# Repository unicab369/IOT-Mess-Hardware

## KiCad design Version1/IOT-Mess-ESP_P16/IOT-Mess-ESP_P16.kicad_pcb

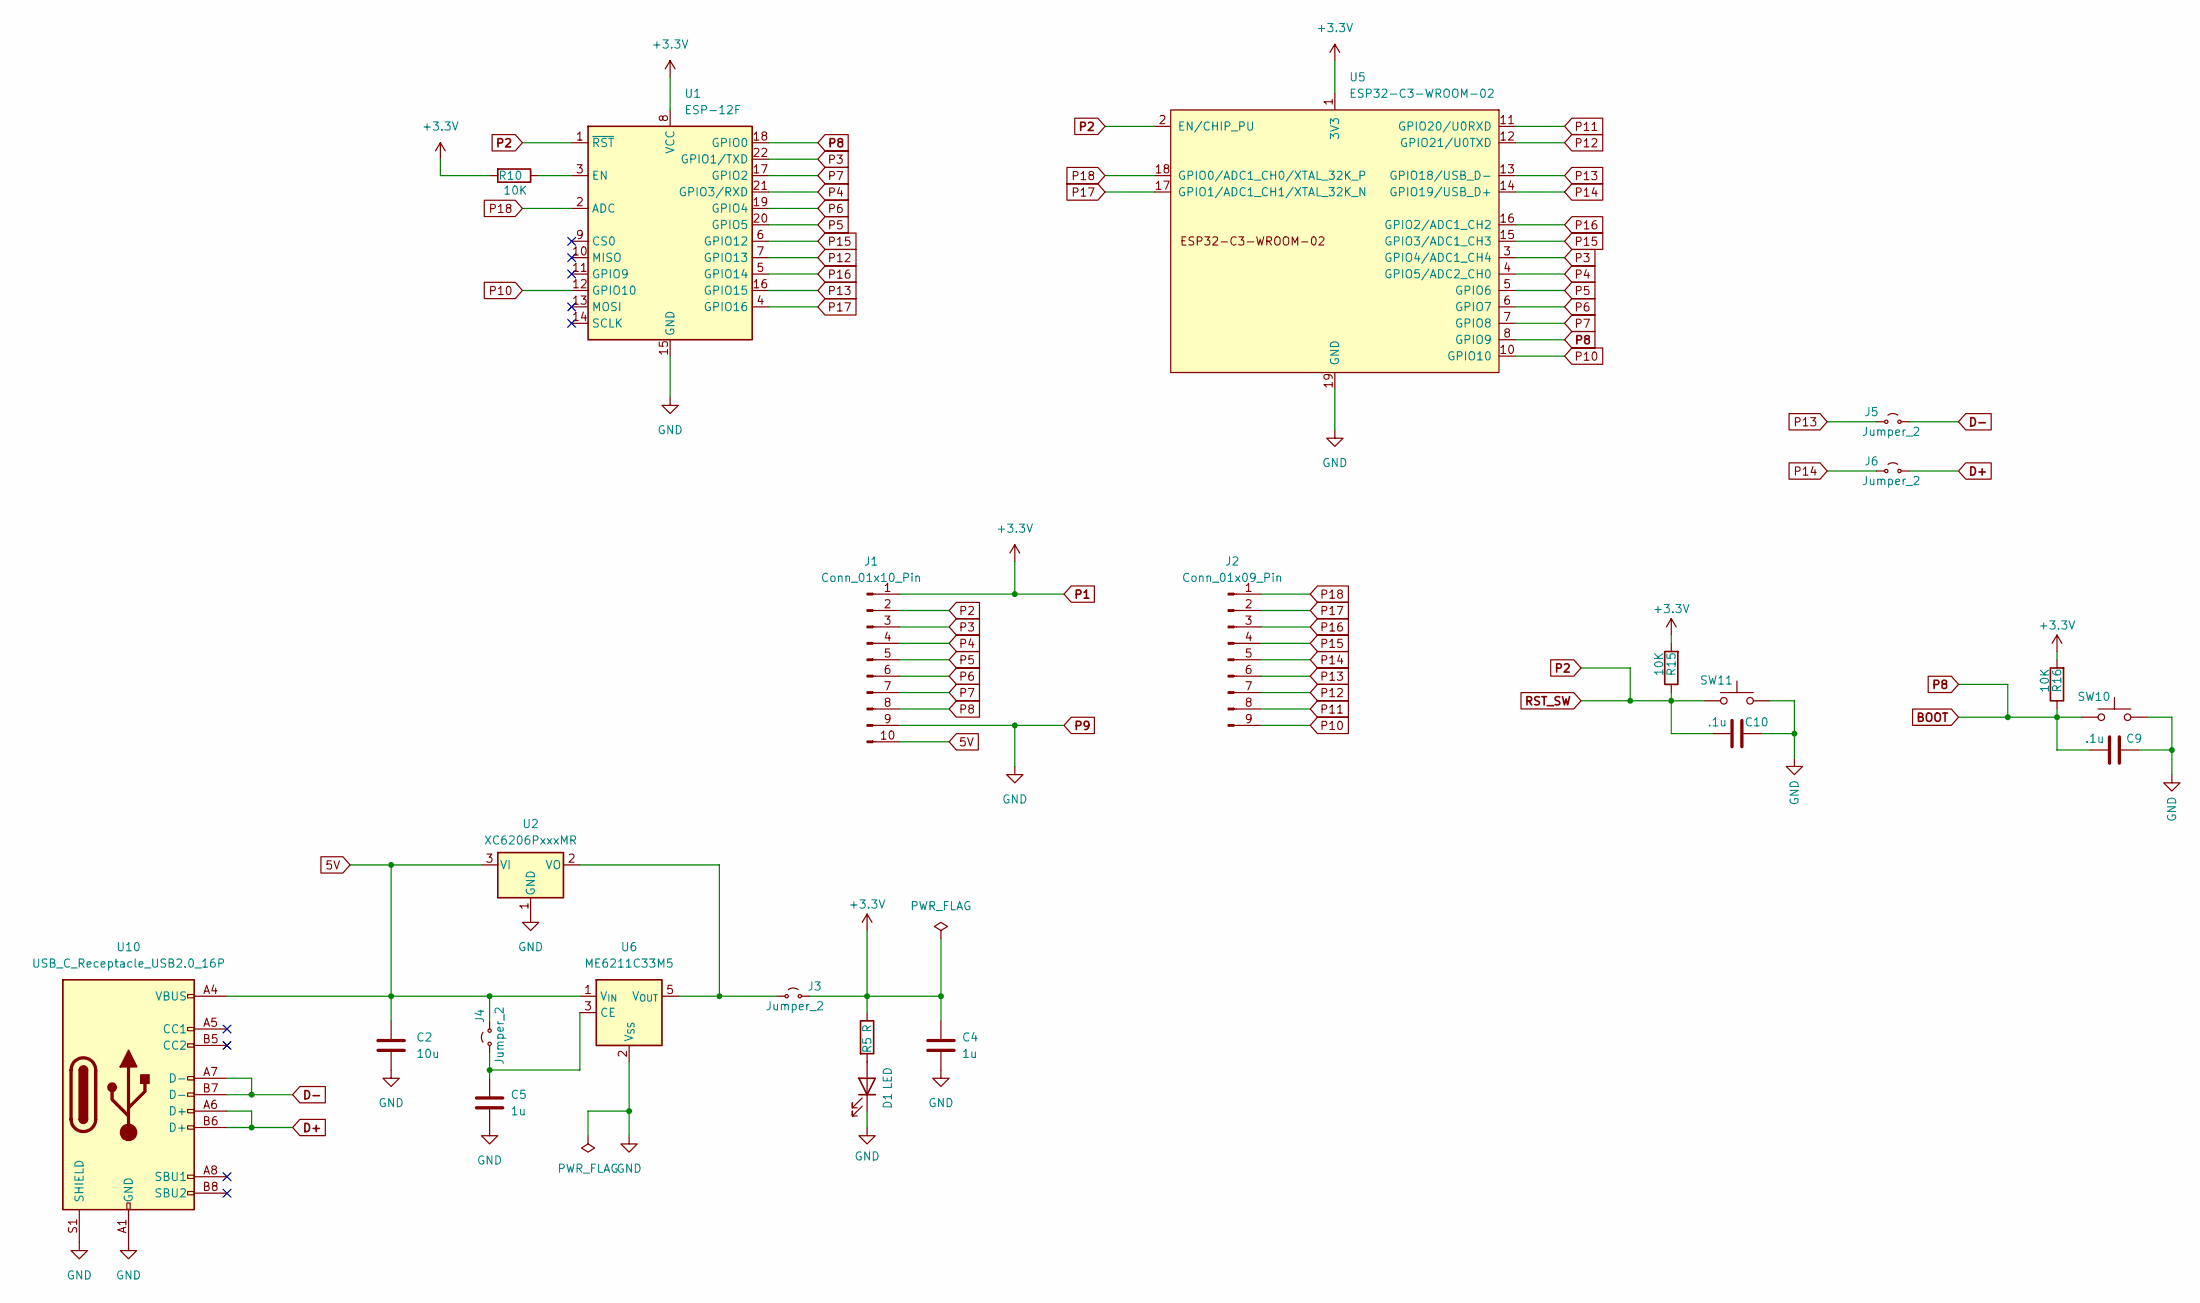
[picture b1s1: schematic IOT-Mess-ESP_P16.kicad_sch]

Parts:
C2: 10u; C_0603_1608Metric
C4, C5: 1u; C_0603_1608Metric
C9, C10: .1u; C_0603_1608Metric
D1: LED; LED_0603_1608Metric
J1: Conn_01x10_Pin; PinHeader_1x10_P2.54mm_Vertical
J2: Conn_01x09_Pin; PinHeader_1x09_P2.54mm_Vertical
J3, J4, J5, J6: Jumper_2; Jumpper-triangle
R5: R; R_0603_1608Metric
R10, R15, R16: 10K; R_0603_1608Metric
SW10, SW11: SW_Push; SW_SPST_PTS810
U1: ESP-12F; ESP-12E
U2: XC6206PxxxMR; SOT-23-3
U5: ESP32-C3-WROOM-02
U6: ME6211C33M5; SOT-23-5
U10: USB_C_Receptacle_USB2.0_16P; USB_C_Receptacle_HRO_TYPE-C-31-M-12

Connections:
5V: C2.1, J1.10, J4.1 (A), U2.3 (VI), U6.1 (V_{IN}), U10.A4 (VBUS), U10.A9 (VBUS), U10.B4 (VBUS), U10.B9 (VBUS)
BOOT: C9.1, J1.8, R16.1, SW10.1, U1.18 (GPIO0), U5.8 (GPIO9)
D+: J6.2 (B), U10.A6 (D+), U10.B6 (D+)
D-: J5.2 (B), U10.A7 (D-), U10.B7 (D-)
unnamed: D1.2 (A), R5.2
unnamed: J3.2 (B), U2.2 (VO), U6.5 (V_{OUT})
unnamed: C5.1, J4.2 (B), U6.3 (CE)
unnamed: R10.1, U1.3 (EN)
P1: C4.1, J1.1, J3.1 (A), R5.1, R10.2, R15.2, R16.2, U1.8 (VCC), U5.1 (3V3)
P2: C10.1, J1.2, R15.1, SW11.1, U1.1 (~RST), U5.2 (EN/CHIP_PU)
P3: J1.3, U1.22 (GPIO1/TXD), U5.3 (GPIO4/ADC1_CH4)
P4: J1.4, U1.21 (GPIO3/RXD), U5.4 (GPIO5/ADC2_CH0)
P5: J1.5, U1.20 (GPIO5), U5.5 (GPIO6)
P6: J1.6, U1.19 (GPIO4), U5.6 (GPIO7)
P7: J1.7, U1.17 (GPIO2), U5.7 (GPIO8)
P9: C2.2, C4.2, C5.2, C9.2, C10.2, D1.1 (K), J1.9, SW10.2, SW11.2, U1.15 (GND), U2.1 (GND), U5.9 (GND), U5.19 (GND), U6.2 (V_{SS}), U10.A1 (GND), U10.A12 (GND), U10.B1 (GND), U10.B12 (GND), U10.S1 (SHIELD)
P10: J2.9, U1.12 (GPIO10), U5.10 (GPIO10)
P11: J2.8, U5.11 (GPIO20/U0RXD)
P12: J2.7, U1.7 (GPIO13), U5.12 (GPIO21/U0TXD)
P13: J2.6, J5.1 (A), U1.16 (GPIO15), U5.13 (GPIO18/USB_D-)
P14: J2.5, J6.1 (A), U5.14 (GPIO19/USB_D+)
P15: J2.4, U1.6 (GPIO12), U5.15 (GPIO3/ADC1_CH3)
P16: J2.3, U1.5 (GPIO14), U5.16 (GPIO2/ADC1_CH2)
P17: J2.2, U1.4 (GPIO16), U5.17 (GPIO1/ADC1_CH1/XTAL_32K_N)
P18: J2.1, U1.2 (ADC), U5.18 (GPIO0/ADC1_CH0/XTAL_32K_P)

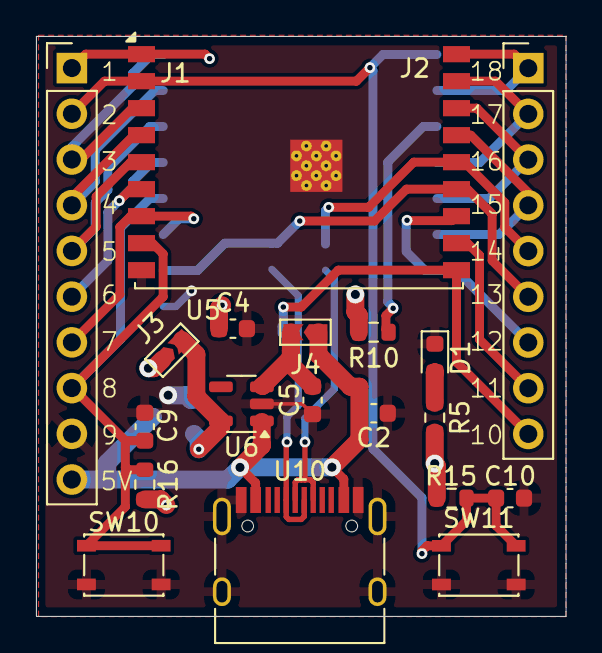
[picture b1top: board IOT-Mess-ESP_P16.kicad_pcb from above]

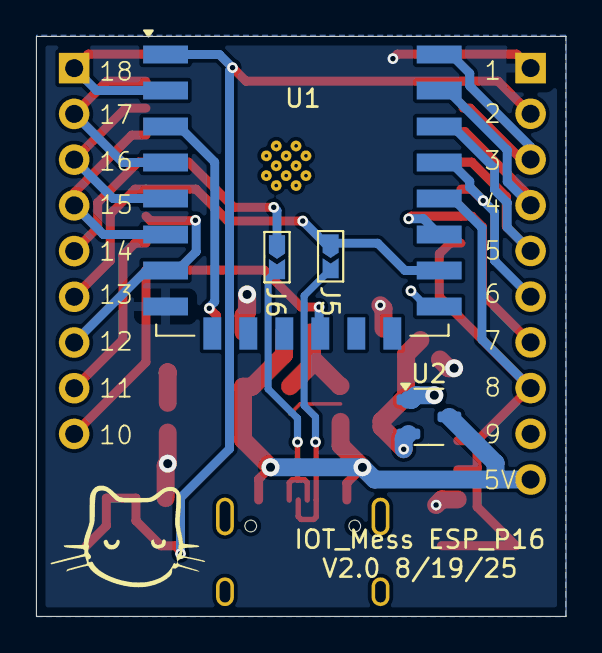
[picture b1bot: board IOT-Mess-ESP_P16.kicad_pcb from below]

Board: 2 copper layers, 29.4 x 32.2 mm, 23 parts (4 on the bottom side), 25 nets.

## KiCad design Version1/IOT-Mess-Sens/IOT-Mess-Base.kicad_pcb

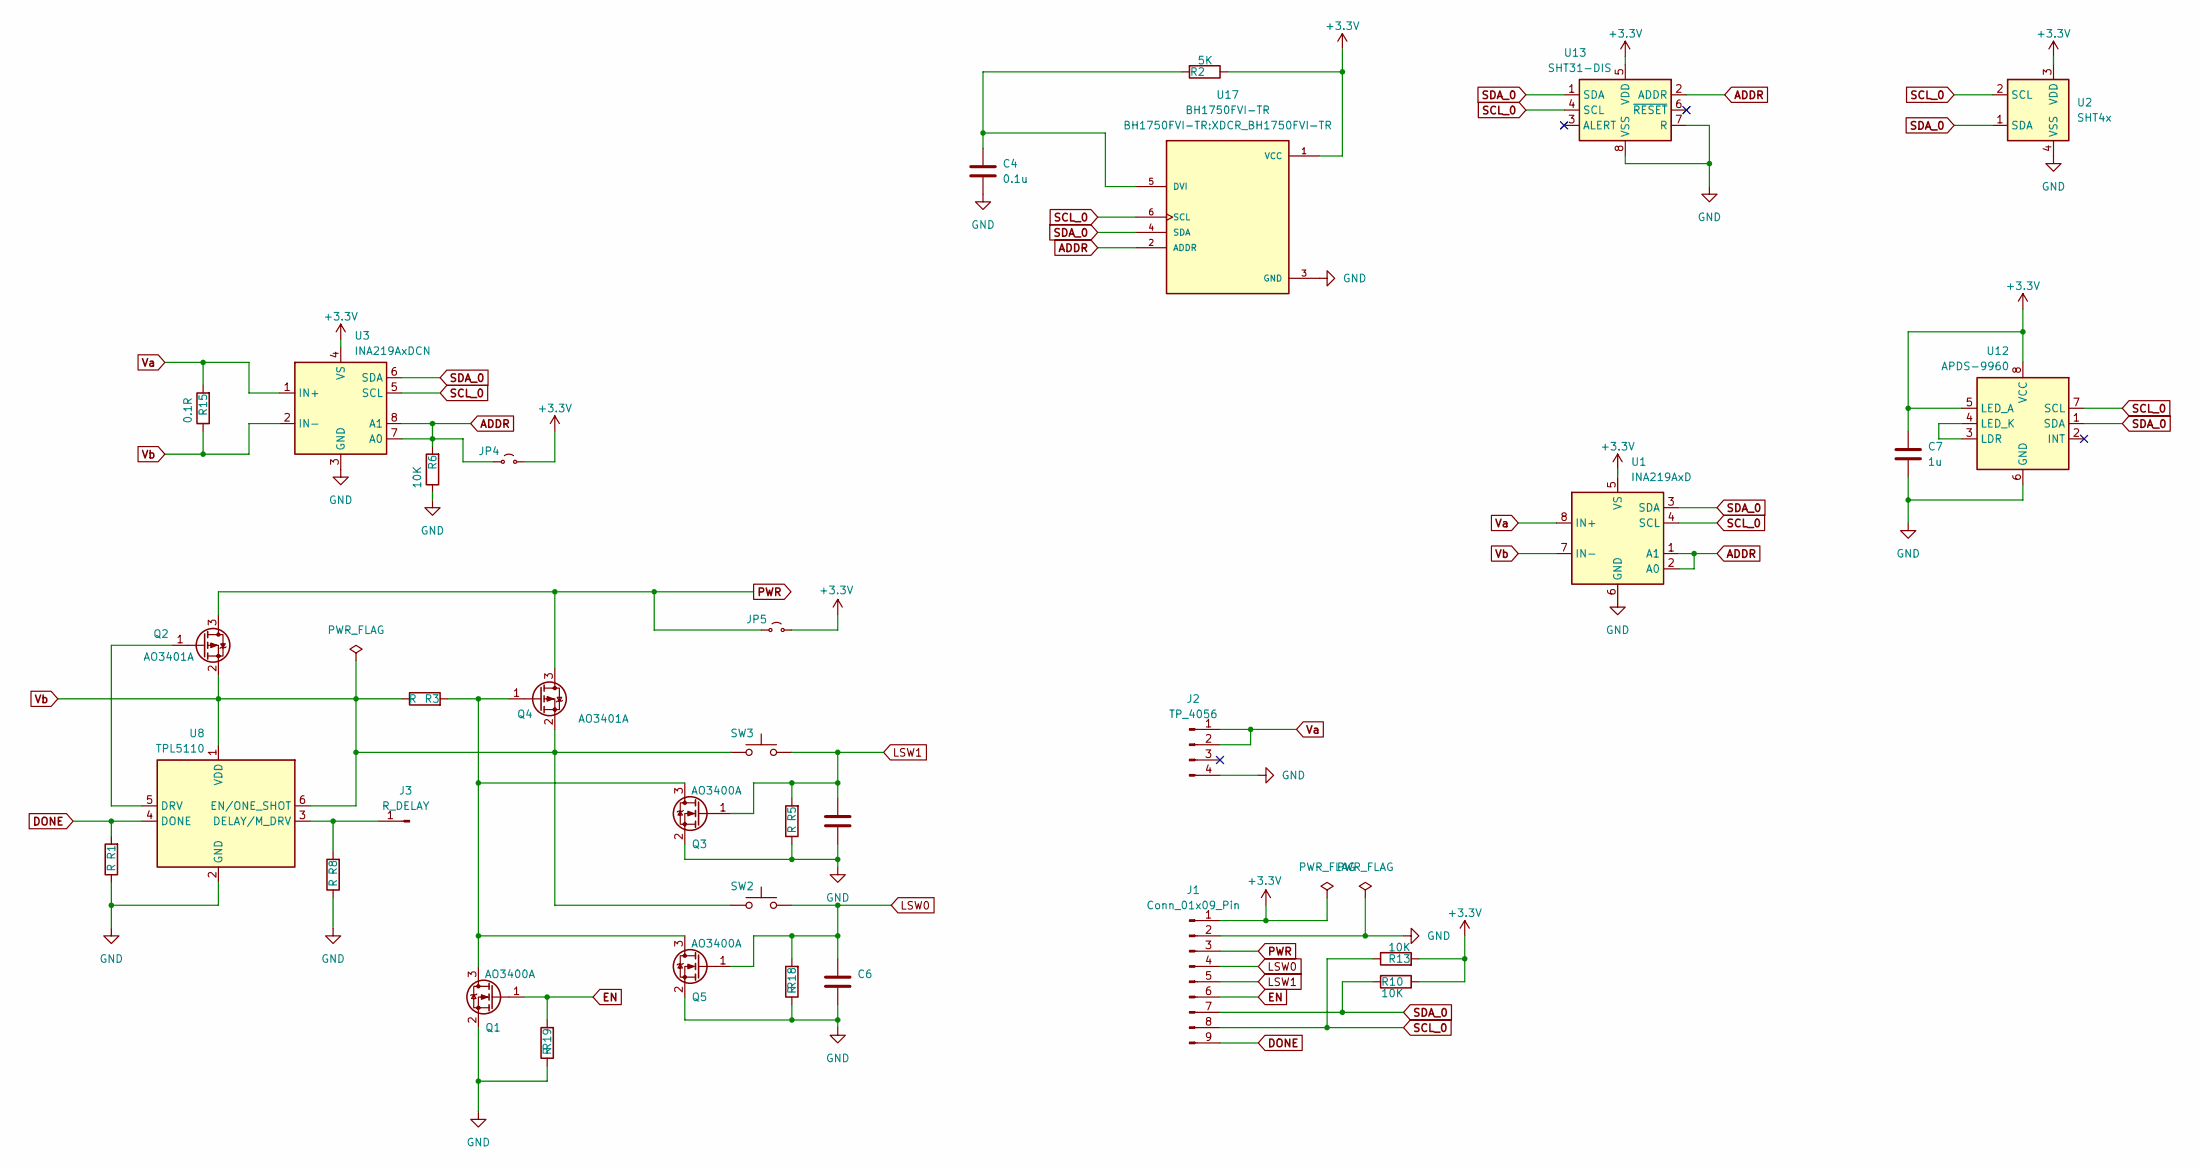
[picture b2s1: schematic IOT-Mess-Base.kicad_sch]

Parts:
C4: 0.1u; C_0603_1608Metric
C5, C6: C; C_0603_1608Metric
C7: 1u; C_0603_1608Metric
J1: Conn_01x09_Pin; PinHeader_1x09_P2.54mm_Vertical
J2: TP_4056; TP_Charger
J3: R_DELAY; PinHeader_1x01_P1.00mm_Vertical
JP4, JP5: Jp_2; SolderJumper-2_P1.3mm_Open_Pad1.0x1.5mm
Q1, Q3, Q5: AO3400A; SOT-23
Q2, Q4: AO3401A; SOT-23
R1, R3, R5, R8, R18, R19: R; R_0603_1608Metric
R2: 5K; R_0603_1608Metric
R6, R10, R13: 10K; R_0603_1608Metric
R15: 0.1R; R_2512_6332Metric
SW2, SW3: SW_Push; SW_SPST_PTS810
U1: INA219AxD; SOIC-8_3.9x4.9mm_P1.27mm
U2: SHT4x; Sensirion_DFN-4_1.5x1.5mm_P0.8mm_SHT4x_NoCentralPad
U3: INA219AxDCN; SOT-23-8
U8: TPL5110; SOT-23-6
U12: APDS-9960; Avago_APDS-9960
U13: SHT31-DIS; Sensirion_DFN-8-1EP_2.5x2.5mm_P0.5mm_EP1.1x1.7mm
U17: BH1750FVI-TR; XDCR_BH1750FVI-TR; PARTREV D

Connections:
+3.3V: C7.1, J1.1, JP4.2 (B), JP5.2 (B), R2.1, R10.1, R13.2, U1.5 (VS), U2.3 (VDD), U3.4 (VS), U12.5 (LED_A), U12.8 (VCC), U13.5 (VDD), U17.1 (VCC)
ADDR: JP4.1 (A), R6.2, U1.1 (A1), U1.2 (A0), U3.7 (A0), U3.8 (A1), U13.2 (ADDR), U17.2 (ADDR)
DONE: J1.9, R1.2, U8.4 (DONE)
EN: J1.6, Q1.1 (G), R19.2
GND: C4.2, C5.2, C6.2, C7.2, J1.2, J2.4, Q1.2 (S), Q3.2 (S), Q5.2 (S), R1.1, R5.1, R6.1, R8.1, R18.1, R19.1, U1.6 (GND), U2.4 (VSS), U3.3 (GND), U8.2 (GND), U12.6 (GND), U13.7 (R), U13.8 (VSS), U13.9 (VSS), U17.3 (GND)
LSW0: C6.1, J1.4, Q5.1 (G), R18.2, SW2.2
LSW1: C5.1, J1.5, Q3.1 (G), R5.2, SW3.2
unnamed: J3.1, R8.2, U8.3 (DELAY/M_DRV)
unnamed: Q1.3 (D), Q3.3 (D), Q4.1 (G), Q5.3 (D), R3.2
unnamed: Q2.1 (G), U8.5 (DRV)
unnamed: U12.3 (LDR), U12.4 (LED_K)
unnamed: C4.1, R2.2, U17.5 (DVI)
PWR: J1.3, JP5.1 (A), Q2.3 (D), Q4.3 (D)
SCL_0: J1.8, R13.1, U1.4 (SCL), U2.2 (SCL), U3.5 (SCL), U12.7 (SCL), U13.4 (SCL), U17.6 (SCL)
SDA_0: J1.7, R10.2, U1.3 (SDA), U2.1 (SDA), U3.6 (SDA), U12.1 (SDA), U13.1 (SDA), U17.4 (SDA)
Va: J2.1, J2.2, R15.2, U1.8 (IN+), U3.1 (IN+)
Vb: Q2.2 (S), Q4.2 (S), R3.1, R15.1, SW2.1, SW3.1, U1.7 (IN-), U3.2 (IN-), U8.1 (VDD), U8.6 (EN/ONE_SHOT)

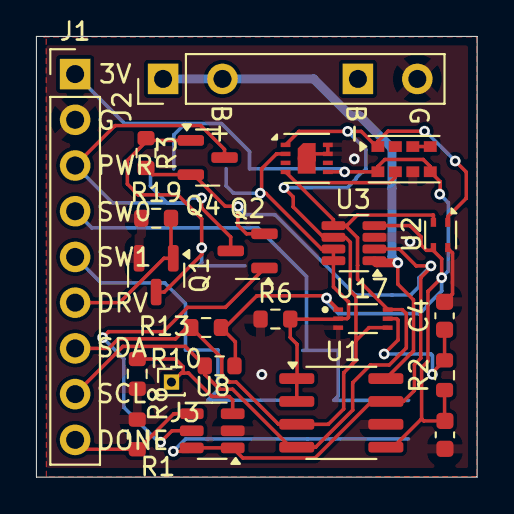
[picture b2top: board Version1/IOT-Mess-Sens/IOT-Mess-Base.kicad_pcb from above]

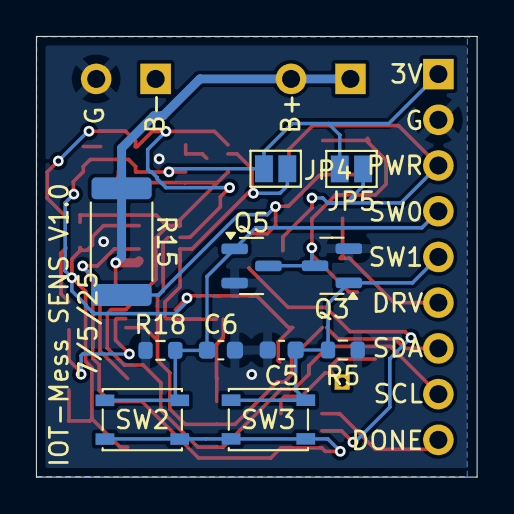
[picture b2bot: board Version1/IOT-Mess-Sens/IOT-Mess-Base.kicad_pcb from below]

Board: 2 copper layers, 24.5 x 24.5 mm, 34 parts (11 on the bottom side), 17 nets.

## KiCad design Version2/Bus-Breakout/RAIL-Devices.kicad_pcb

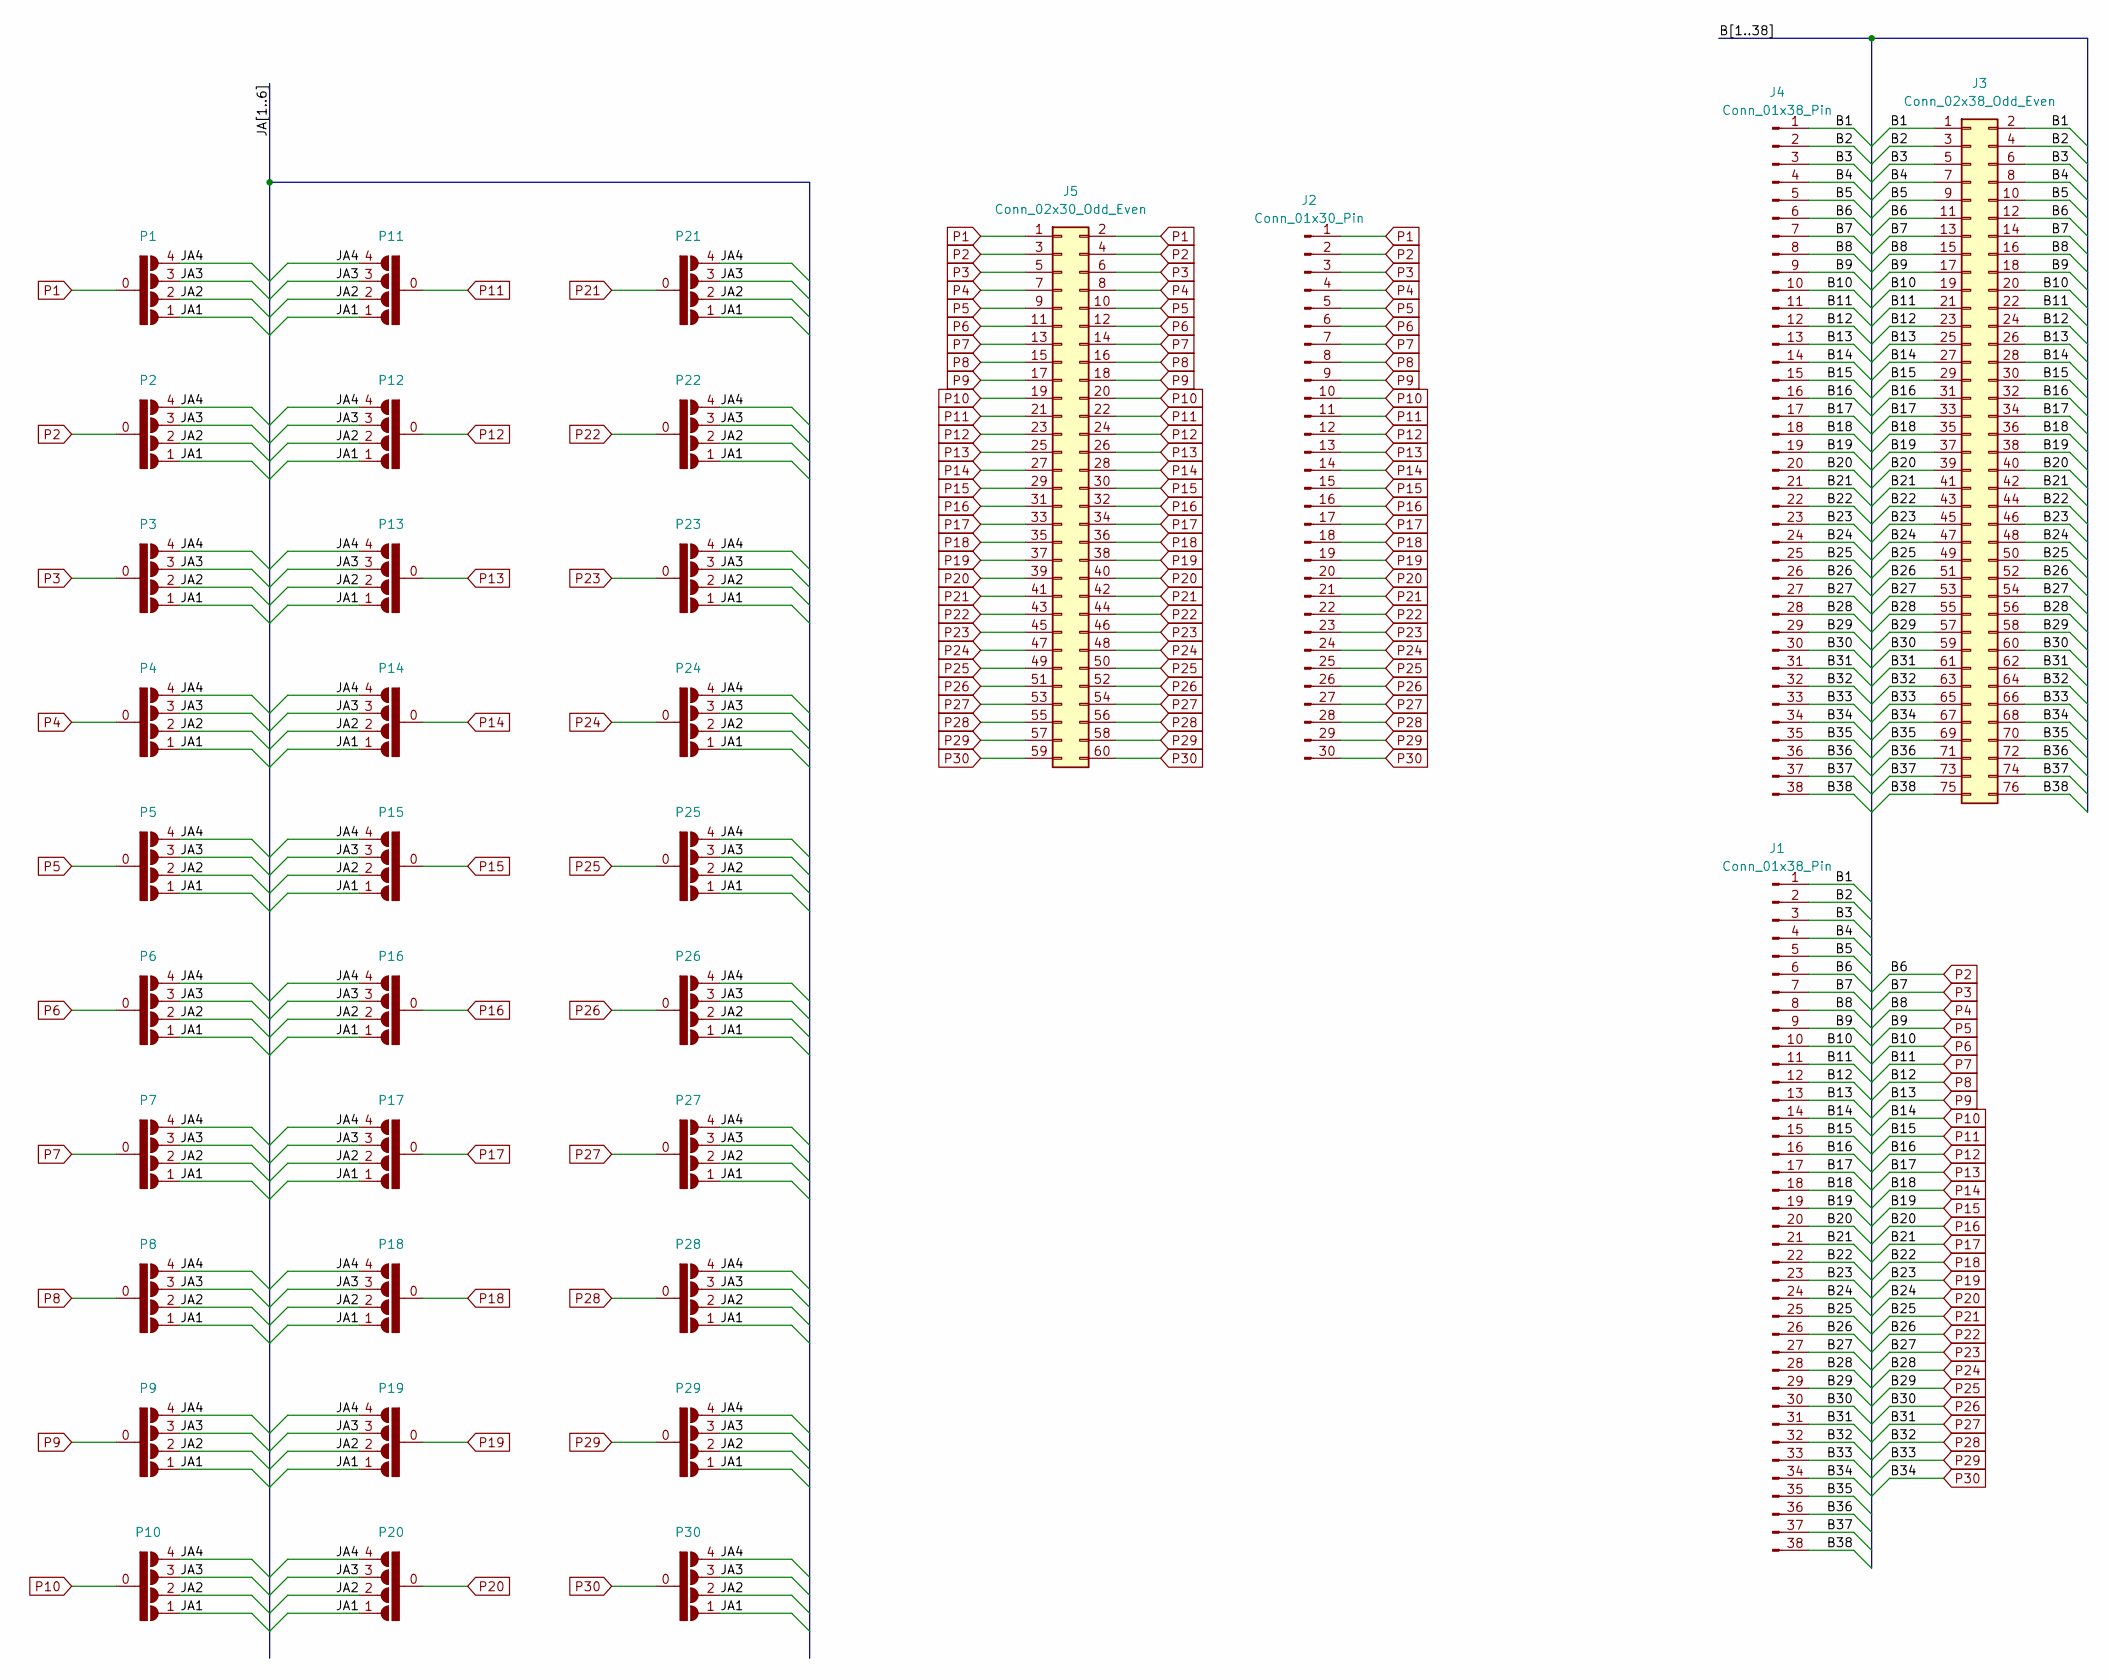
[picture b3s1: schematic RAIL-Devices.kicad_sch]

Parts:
J1, J4: Conn_01x38_Pin; PinSocket_1x38_P2.54mm_Vertical
J2: Conn_01x30_Pin; PinSocket_1x30_P2.54mm_Vertical
J3: Conn_02x38_Odd_Even; PinSocket_2x38_P2.54mm_Vertical
J5: Conn_02x30_Odd_Even; PinSocket_2x30_P2.54mm_Vertical
P1, P2, P3, P4, P5, P6, P7, P8, P9, P10, P11, P12, P13, P14, P15, P16, P17, P18, P19, P20, P21, P22, P23, P24, P25, P26, P27, P28, P29, P30: Jumper4x1

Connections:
/B1: J1.1, J3.1, J3.2, J4.1
/B2: J1.2, J3.3, J3.4, J4.2
/B3: J1.3, J3.5, J3.6, J4.3
/B4: J1.4, J3.7, J3.8, J4.4
/B5: J1.5, J3.9, J3.10, J4.5
/B35: J1.35, J3.69, J3.70, J4.35
/B36: J1.36, J3.71, J3.72, J4.36
/B37: J1.37, J3.73, J3.74, J4.37
/B38: J1.38, J3.75, J3.76, J4.38
/JA1: P1.1 (B), P2.1 (B), P3.1 (B), P4.1 (B), P5.1 (B), P6.1 (B), P7.1 (B), P8.1 (B), P9.1 (B), P10.1 (B), P11.1 (B), P12.1 (B), P13.1 (B), P14.1 (B), P15.1 (B), P16.1 (B), P17.1 (B), P18.1 (B), P19.1 (B), P20.1 (B), P21.1 (B), P22.1 (B), P23.1 (B), P24.1 (B), P25.1 (B), P26.1 (B), P27.1 (B), P28.1 (B), P29.1 (B), P30.1 (B)
/JA2: P1.2 (B), P2.2 (B), P3.2 (B), P4.2 (B), P5.2 (B), P6.2 (B), P7.2 (B), P8.2 (B), P9.2 (B), P10.2 (B), P11.2 (B), P12.2 (B), P13.2 (B), P14.2 (B), P15.2 (B), P16.2 (B), P17.2 (B), P18.2 (B), P19.2 (B), P20.2 (B), P21.2 (B), P22.2 (B), P23.2 (B), P24.2 (B), P25.2 (B), P26.2 (B), P27.2 (B), P28.2 (B), P29.2 (B), P30.2 (B)
/JA3: P1.3 (B), P2.3 (B), P3.3 (B), P4.3 (B), P5.3 (B), P6.3 (B), P7.3 (B), P8.3 (B), P9.3 (B), P10.3 (B), P11.3 (B), P12.3 (B), P13.3 (B), P14.3 (B), P15.3 (B), P16.3 (B), P17.3 (B), P18.3 (B), P19.3 (B), P20.3 (B), P21.3 (B), P22.3 (B), P23.3 (B), P24.3 (B), P25.3 (B), P26.3 (B), P27.3 (B), P28.3 (B), P29.3 (B), P30.3 (B)
/JA4: P1.4 (B), P2.4 (B), P3.4 (B), P4.4 (B), P5.4 (B), P6.4 (B), P7.4 (B), P8.4 (B), P9.4 (B), P10.4 (B), P11.4 (B), P12.4 (B), P13.4 (B), P14.4 (B), P15.4 (B), P16.4 (B), P17.4 (B), P18.4 (B), P19.4 (B), P20.4 (B), P21.4 (B), P22.4 (B), P23.4 (B), P24.4 (B), P25.4 (B), P26.4 (B), P27.4 (B), P28.4 (B), P29.4 (B), P30.4 (B)
P1: J2.1, J5.1, J5.2, P1.0 (C)
P2: J1.6, J2.2, J3.11, J3.12, J4.6, J5.3, J5.4, P2.0 (C)
P3: J1.7, J2.3, J3.13, J3.14, J4.7, J5.5, J5.6, P3.0 (C)
P4: J1.8, J2.4, J3.15, J3.16, J4.8, J5.7, J5.8, P4.0 (C)
P5: J1.9, J2.5, J3.17, J3.18, J4.9, J5.9, J5.10, P5.0 (C)
P6: J1.10, J2.6, J3.19, J3.20, J4.10, J5.11, J5.12, P6.0 (C)
P7: J1.11, J2.7, J3.21, J3.22, J4.11, J5.13, J5.14, P7.0 (C)
P8: J1.12, J2.8, J3.23, J3.24, J4.12, J5.15, J5.16, P8.0 (C)
P9: J1.13, J2.9, J3.25, J3.26, J4.13, J5.17, J5.18, P9.0 (C)
P10: J1.14, J2.10, J3.27, J3.28, J4.14, J5.19, J5.20, P10.0 (C)
P11: J1.15, J2.11, J3.29, J3.30, J4.15, J5.21, J5.22, P11.0 (C)
P12: J1.16, J2.12, J3.31, J3.32, J4.16, J5.23, J5.24, P12.0 (C)
P13: J1.17, J2.13, J3.33, J3.34, J4.17, J5.25, J5.26, P13.0 (C)
P14: J1.18, J2.14, J3.35, J3.36, J4.18, J5.27, J5.28, P14.0 (C)
P15: J1.19, J2.15, J3.37, J3.38, J4.19, J5.29, J5.30, P15.0 (C)
P16: J1.20, J2.16, J3.39, J3.40, J4.20, J5.31, J5.32, P16.0 (C)
P17: J1.21, J2.17, J3.41, J3.42, J4.21, J5.33, J5.34, P17.0 (C)
P18: J1.22, J2.18, J3.43, J3.44, J4.22, J5.35, J5.36, P18.0 (C)
P19: J1.23, J2.19, J3.45, J3.46, J4.23, J5.37, J5.38, P19.0 (C)
P20: J1.24, J2.20, J3.47, J3.48, J4.24, J5.39, J5.40, P20.0 (C)
P21: J1.25, J2.21, J3.49, J3.50, J4.25, J5.41, J5.42, P21.0 (C)
P22: J1.26, J2.22, J3.51, J3.52, J4.26, J5.43, J5.44, P22.0 (C)
P23: J1.27, J2.23, J3.53, J3.54, J4.27, J5.45, J5.46, P23.0 (C)
P24: J1.28, J2.24, J3.55, J3.56, J4.28, J5.47, J5.48, P24.0 (C)
P25: J1.29, J2.25, J3.57, J3.58, J4.29, J5.49, J5.50, P25.0 (C)
P26: J1.30, J2.26, J3.59, J3.60, J4.30, J5.51, J5.52, P26.0 (C)
P27: J1.31, J2.27, J3.61, J3.62, J4.31, J5.53, J5.54, P27.0 (C)
P28: J1.32, J2.28, J3.63, J3.64, J4.32, J5.55, J5.56, P28.0 (C)
P29: J1.33, J2.29, J3.65, J3.66, J4.33, J5.57, J5.58, P29.0 (C)
P30: J1.34, J2.30, J3.67, J3.68, J4.34, J5.59, J5.60, P30.0 (C)

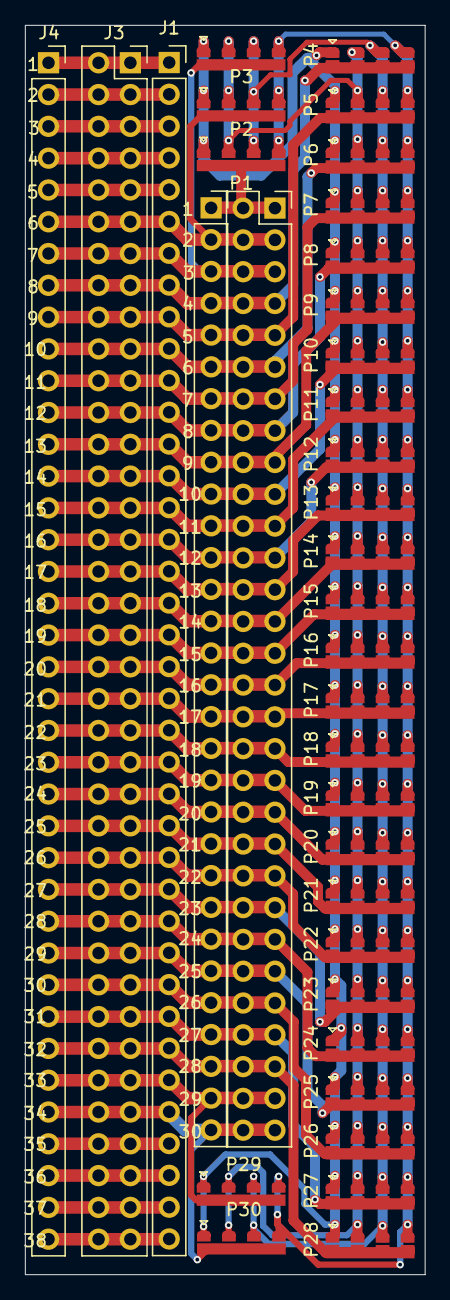
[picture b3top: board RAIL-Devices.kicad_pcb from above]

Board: 2 copper layers, 31.9 x 99.8 mm, 35 parts (0 on the bottom side), 43 nets.

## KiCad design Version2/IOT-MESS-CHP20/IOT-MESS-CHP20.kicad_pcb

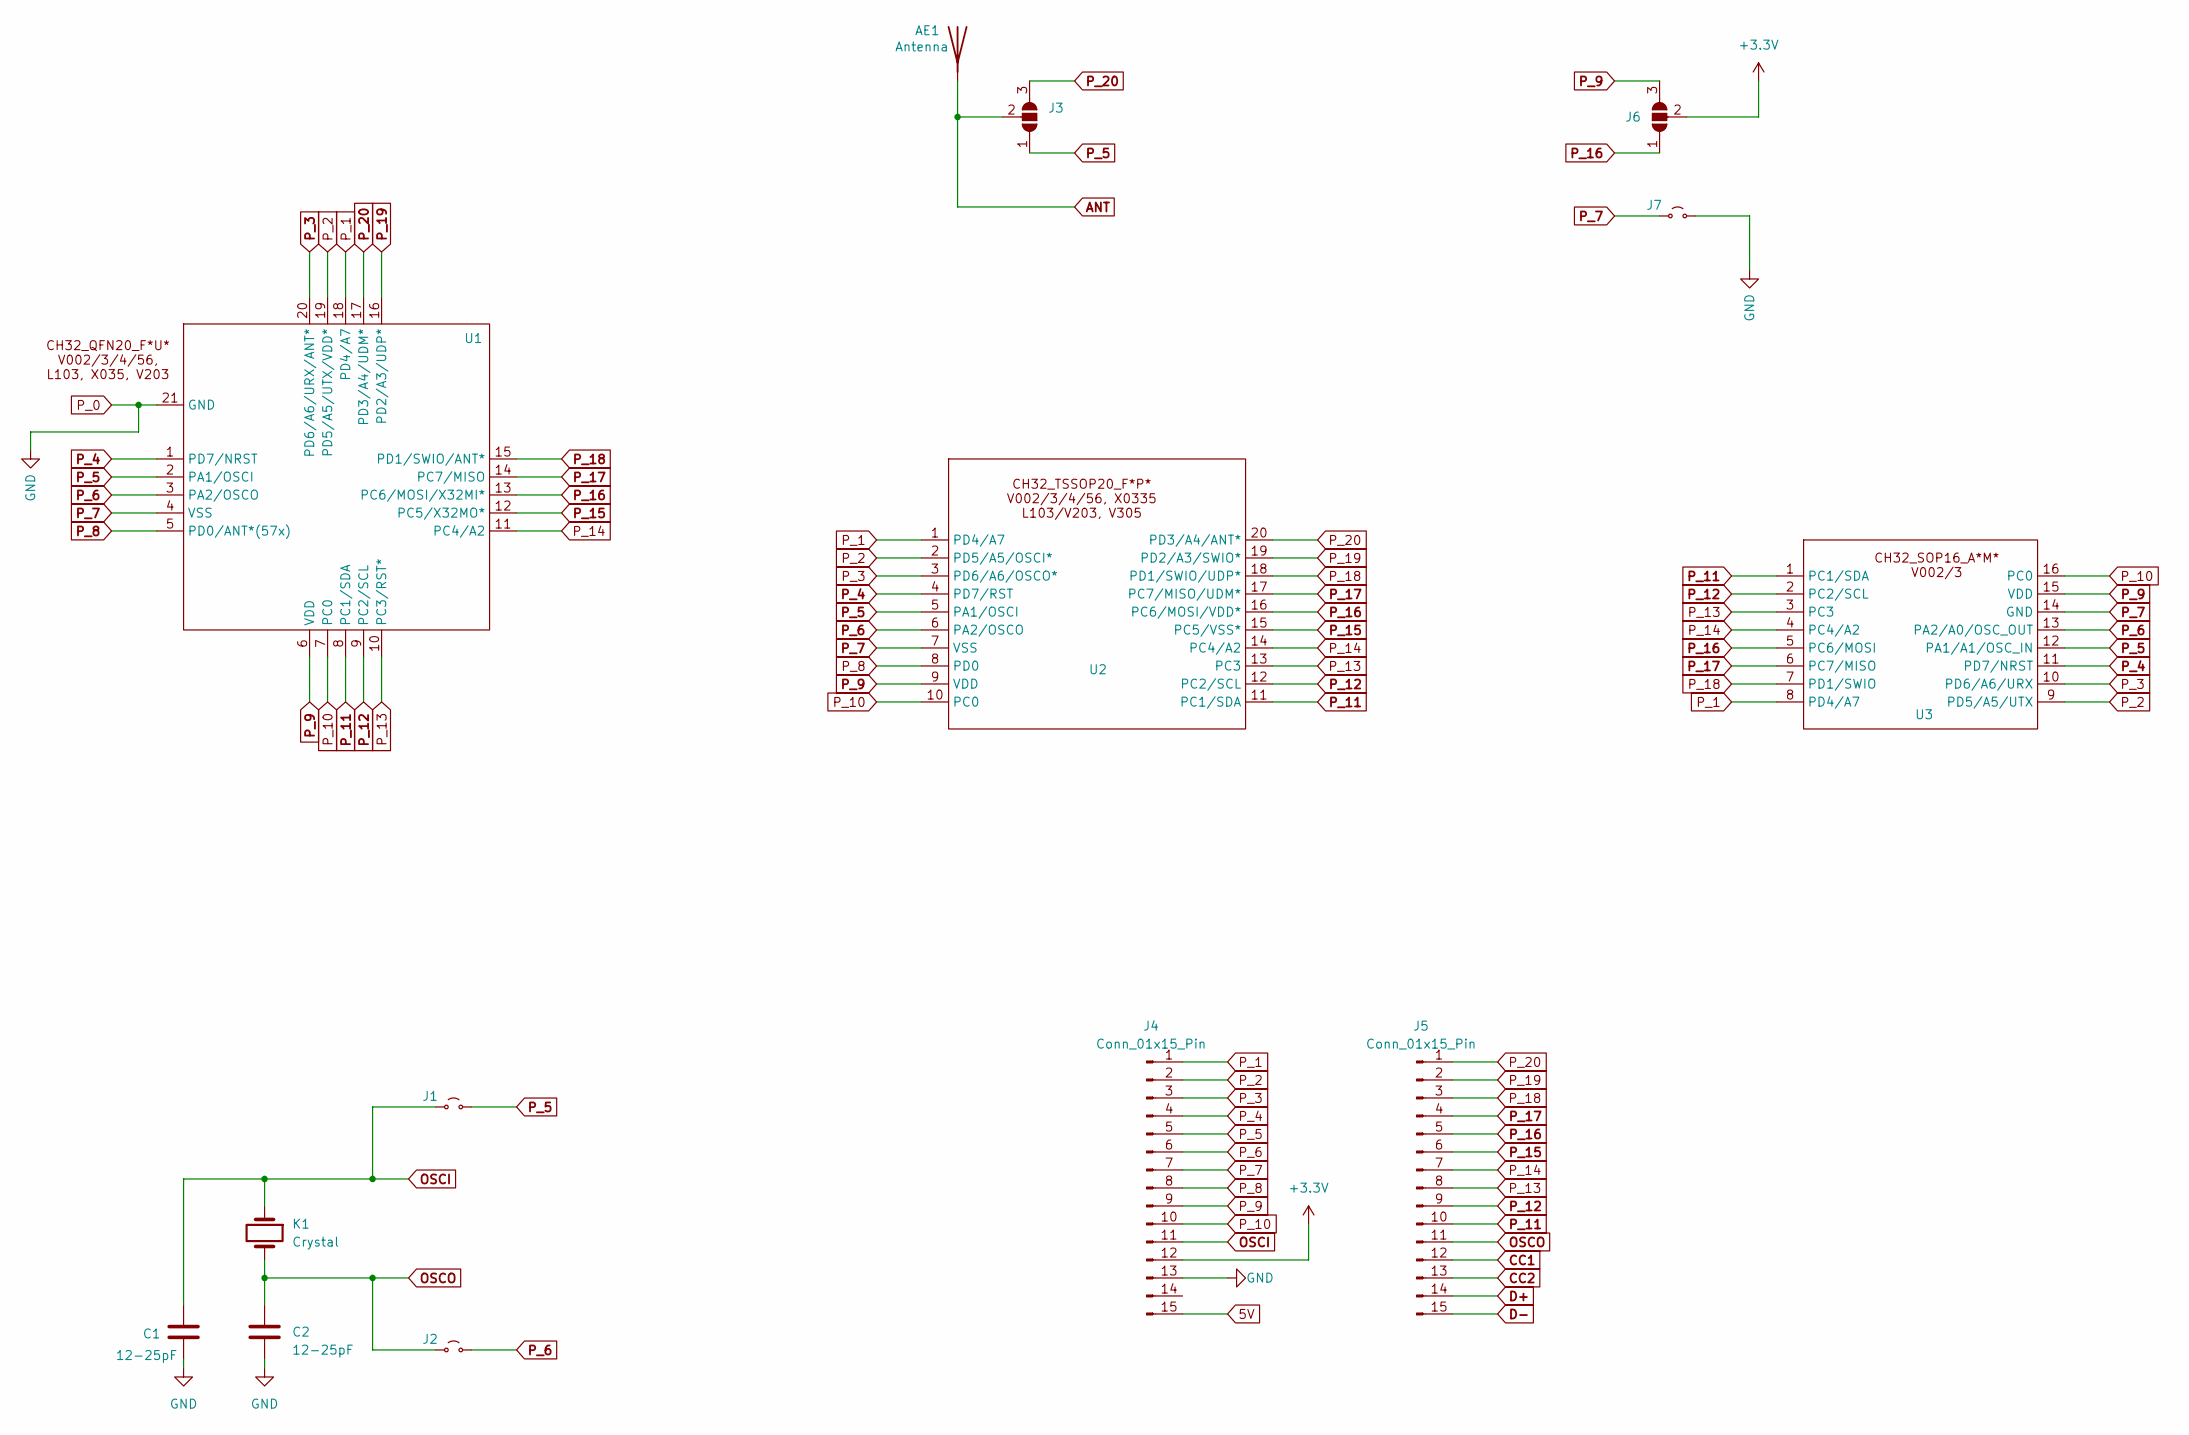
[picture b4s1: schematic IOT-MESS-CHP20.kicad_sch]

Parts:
AE1: Antenna; Texas_SWRA117D_2.4GHz_Right
C1, C2: 12-25pF; C_0603_1608Metric
J1, J2, J7: Jumper_2; Jumpper-triangle
J3, J6: Jumper; Jumper-3_P1.3mm_Open_RoundedPad1.0x1.5mm
J4, J5: Conn_01x15_Pin; PinHeader_1x15_P2.54mm_Vertical
K1: Crystal; Crystal_SMD_3225-4Pin_3.2x2.5mm
U1: QFN-20-1EP_3x3mm_P0.4mm_EP1.65x1.65mm_ThermalVias
U2: TSSOP-20_4.4x6.5mm_P0.65mm
U3: SOP-16_3.9x9.9mm_P1.27mm

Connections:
5V: J4.15
+3.3V: J4.12, J6.2 (C)
ANT: AE1.1 (A), J3.2 (C)
CC1: J5.12
CC2: J5.13
D+: J5.14
D-: J5.15
OSCI: C1.1, J1.1 (A), J4.11, K1.1
OSCO: C2.1, J2.1 (A), J5.11, K1.2
P_0: C1.2, C2.2, J4.13, J7.2 (B), U1.21 (GND)
P_1: J4.1, U1.18 (PD4/A7), U2.1 (PD4/A7), U3.8 (PD4/A7)
P_2: J4.2, U1.19 (PD5/A5/UTX/VDD*), U2.2 (PD5/A5/OSCI*), U3.9 (PD5/A5/UTX)
P_3: J4.3, U1.20 (PD6/A6/URX/ANT*), U2.3 (PD6/A6/OSCO*), U3.10 (PD6/A6/URX)
P_4: J4.4, U1.1 (PD7/NRST), U2.4 (PD7/RST), U3.11 (PD7/NRST)
P_5: J1.2 (B), J3.1 (A), J4.5, U1.2 (PA1/OSCI), U2.5 (PA1/OSCI), U3.12 (PA1/A1/OSC_IN)
P_6: J2.2 (B), J4.6, U1.3 (PA2/OSCO), U2.6 (PA2/OSCO), U3.13 (PA2/A0/OSC_OUT)
P_7: J4.7, J7.1 (A), U1.4 (VSS), U2.7 (VSS), U3.14 (GND)
P_8: J4.8, U1.5 (PD0/ANT*(57x)), U2.8 (PD0)
P_9: J4.9, J6.3 (B), U1.6 (VDD), U2.9 (VDD), U3.15 (VDD)
P_10: J4.10, U1.7 (PC0), U2.10 (PC0), U3.16 (PC0)
P_11: J5.10, U1.8 (PC1/SDA), U2.11 (PC1/SDA), U3.1 (PC1/SDA)
P_12: J5.9, U1.9 (PC2/SCL), U2.12 (PC2/SCL), U3.2 (PC2/SCL)
P_13: J5.8, U1.10 (PC3/RST*), U2.13 (PC3), U3.3 (PC3)
P_14: J5.7, U1.11 (PC4/A2), U2.14 (PC4/A2), U3.4 (PC4/A2)
P_15: J5.6, U1.12 (PC5/X32MO*), U2.15 (PC5/VSS*)
P_16: J5.5, J6.1 (A), U1.13 (PC6/MOSI/X32MI*), U2.16 (PC6/MOSI/VDD*), U3.5 (PC6/MOSI)
P_17: J5.4, U1.14 (PC7/MISO), U2.17 (PC7/MISO/UDM*), U3.6 (PC7/MISO)
P_18: J5.3, U1.15 (PD1/SWIO/ANT*), U2.18 (PD1/SWIO/UDP*), U3.7 (PD1/SWIO)
P_19: J5.2, U1.16 (PD2/A3/UDP*), U2.19 (PD2/A3/SWIO*)
P_20: J3.3 (B), J5.1, U1.17 (PD3/A4/UDM*), U2.20 (PD3/A4/ANT*)

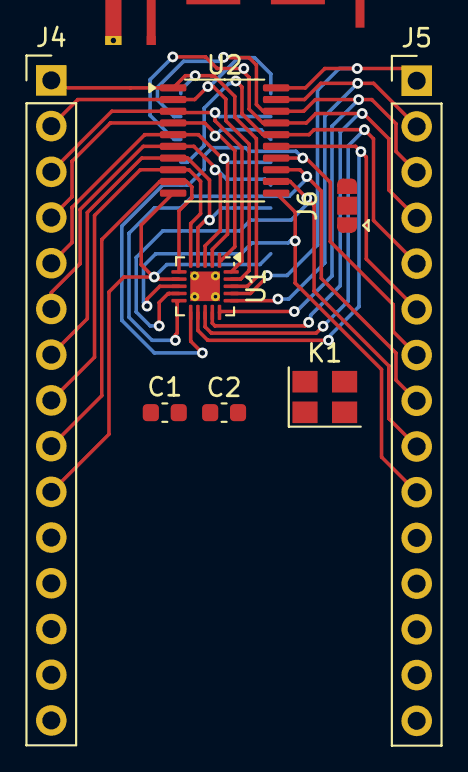
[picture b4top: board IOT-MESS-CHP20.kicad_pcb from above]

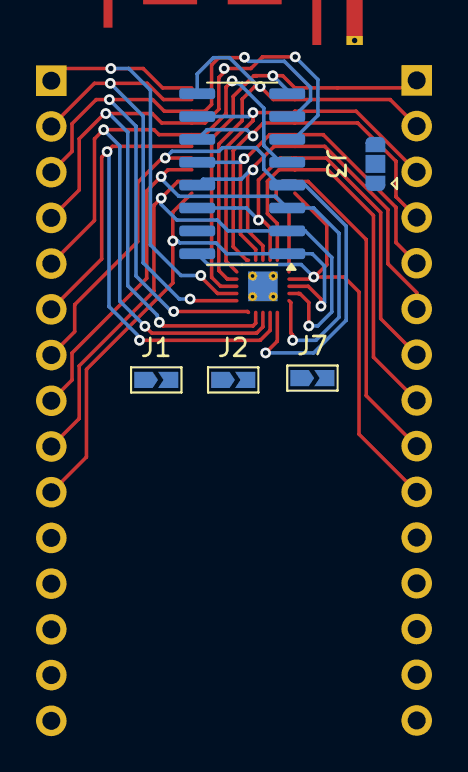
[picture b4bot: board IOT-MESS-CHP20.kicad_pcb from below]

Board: 2 copper layers, 14 parts (5 on the bottom side), 25 nets.
